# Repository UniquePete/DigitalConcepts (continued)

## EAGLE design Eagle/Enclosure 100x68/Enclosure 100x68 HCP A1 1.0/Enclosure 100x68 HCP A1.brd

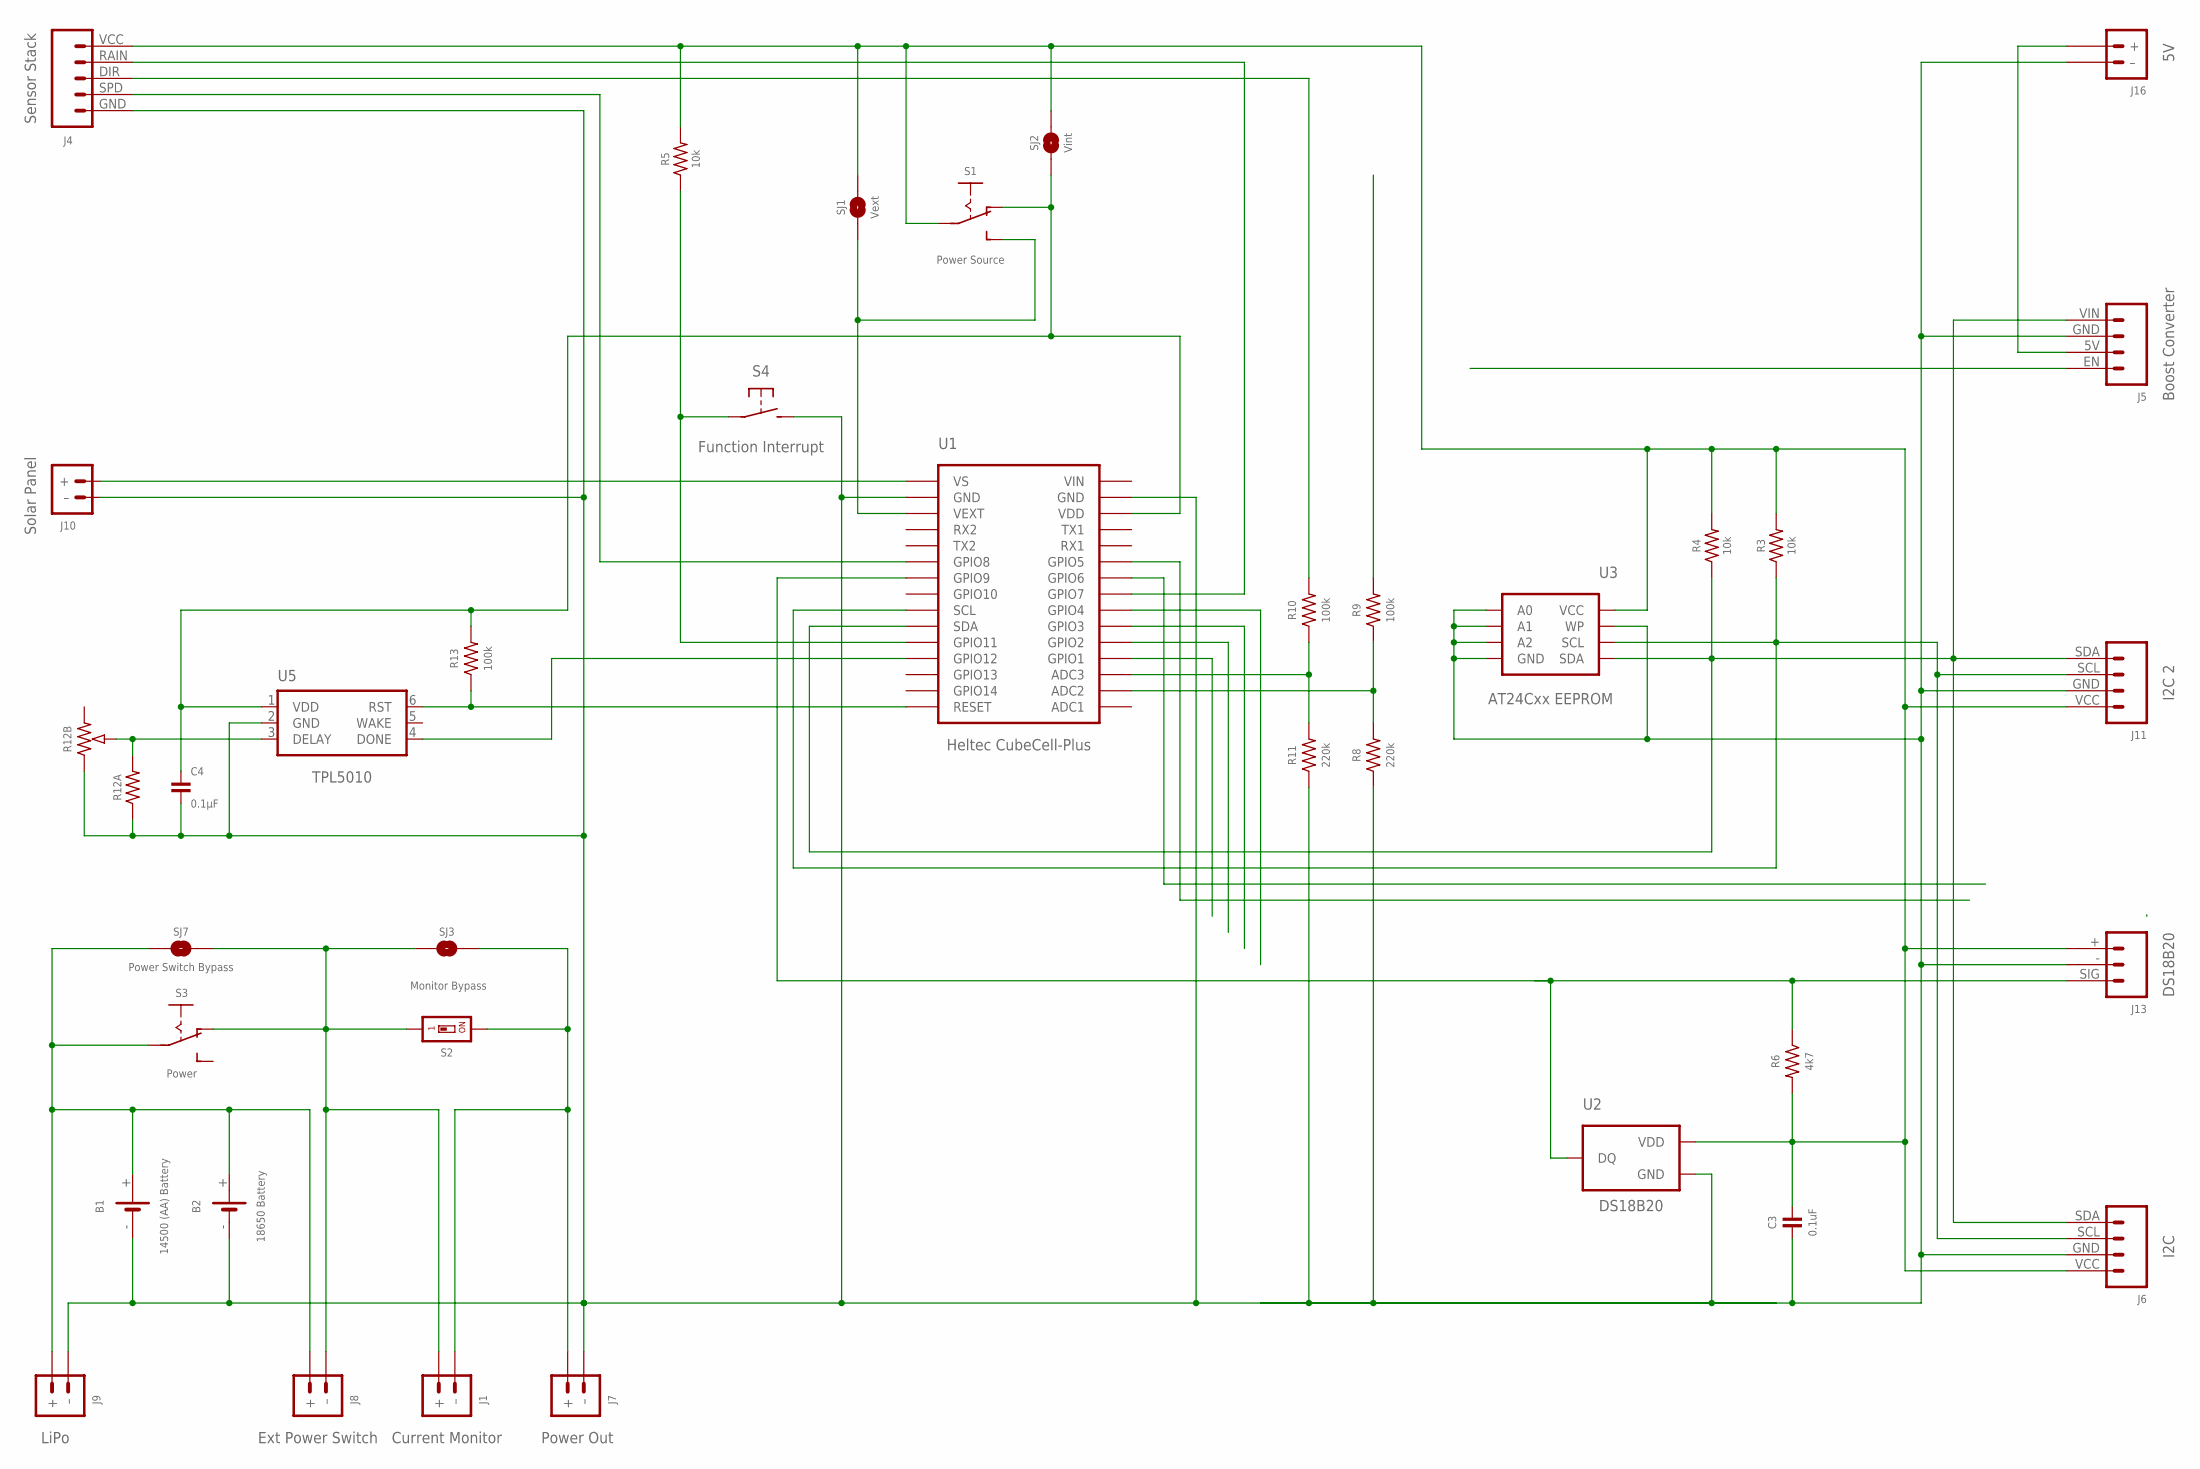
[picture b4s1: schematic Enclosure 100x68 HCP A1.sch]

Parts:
B1: 14500 (AA) Battery; BATTERY-14500
B2: 18650 Battery; BATTERY-18650
C3: 0.1uF; C0805
C4: 0.1µF; C0805
J1: Current Monitor; JST-PH2.0-2-HORIZONTAL
J4: Sensor Stack; JST-PH2.0-5-DUAL-WEATHER
J5: Boost Converter; CONN_04-FP6277
J6: I2C; CONN_04-I2C
J7: Power Out; JST-GH1.25-2-HORIZONTAL
J8: Ext Power Switch; JST-PH2.0-2-DUAL-POWER
J9: LiPo; JST-PH2.0-2-HORIZONTAL-POWER@1
J10: Solar Panel; JST-PH2.0-2-VERTICAL=POWER
J11: I2C 2; JST-PH2.0-4-HORIZONTAL
J13: DS18B20; JST-PH2.0-3-HORIZONTAL-DS18B20
J16: 5V; JST-PH2.0-2-HORIZONTAL-POWER
R3, R4, R5: 10k; R0805
R6: 4k7; R0805
R8, R11: 220k; R0805
R9, R10, R13: 100k; R0805
R12A: RESISTORR0805; R0805
R12B: RESISTOR-TRIMM-33-US; RTRIM3*3
S1: Power Source; SWITCH-SPDT-SMT
S2: Monitor Bypass; SMD-001
S3: Power; SWITCH-SPDT-PTH
S4: Function Interrupt; SWITCH-2-PAD
SJ1: Vext; SJ
SJ2: Vint; SJ-VIA-12
SJ3: Monitor; SJ
SJ7: Power Switch Bypass; SJ
U1: Heltec CubeCell-Plus; HELTEC-CUBECELL=PLUS-X
U2: DS18B20; TO-92
U3: AT24Cxx EEPROM; SOP-8
U5: TPL5010; SOT-23-6

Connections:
GND: B1.-, B2.-, C3.2, C4.2, J4.GND (5), J5.GND (3), J6.GND (2), J7.- (–), J9.- (–), J10.- (–), J11.GND (2), J13.- (2), J16.- (–), R8.1, R11.1, R12A.1, R12B.1 (A), S4.P$2 (S), U1.GND@14 (GND), U1.GND@17 (GND), U2.1 (GND), U3.P$1 (A0), U3.P$2 (A1), U3.P$3 (A2), U3.P$4 (GND), U3.P$7 (WP), U5.2 (GND)
unnamed: J10.+, U1.VS
unnamed: R10.1, R11.2, U1.ADC3
unnamed: J1.2 (–), J7.+, S2.2, SJ3.1
unnamed: B1.+, B2.+, J8.+, J9.+, S3.2, SJ7.2
unnamed: J4.DIR (3), R10.2
unnamed: J6.SCL (3), J11.SCL (3), R3.1, U1.SCL, U3.P$6 (SCL)
unnamed: J5.VIN (4), J6.SDA (4), J11.SDA (4), R4.1, U1.SDA, U3.P$5 (SDA)
unnamed: J4.SPD (4), U1.GPIO8
unnamed: S1.3 (S), SJ1.1, U1.VEXT
unnamed: R12A.2, R12B.2 (S), U5.3 (DELAY)
unnamed: J5.5V (2), J16.+
unnamed: J1.1 (+), J8.- (–), S2.1, S3.1 (O), SJ3.2, SJ7.1
unnamed: J13.SIG (1), R6.1, U1.GPIO9, U2.2 (DQ)
unnamed: R5.1, S4.P$1, U1.GPIO11
unnamed: J4.RAIN (2), U1.GPIO7
unnamed: R8.2, R9.1, U1.ADC2
unnamed: R13.1, U1.RST (RESET), U5.6 (RST)
unnamed: U1.GPIO12, U5.4 (DONE)
unnamed: C4.1, R13.2, S1.1 (O), SJ2.1, SJ2.1@V (1), U1.VDD, U5.1 (VDD)
VEXT: C3.1, J4.VCC (1), J6.VCC (1), J11.VCC (1), J13.+ (3), R3.2, R4.2, R5.2, R6.2, S1.2, SJ1.2, SJ2.2, SJ2.2@V (2), U2.3 (VDD), U3.P$8 (VCC)
VIN: U1.VIN

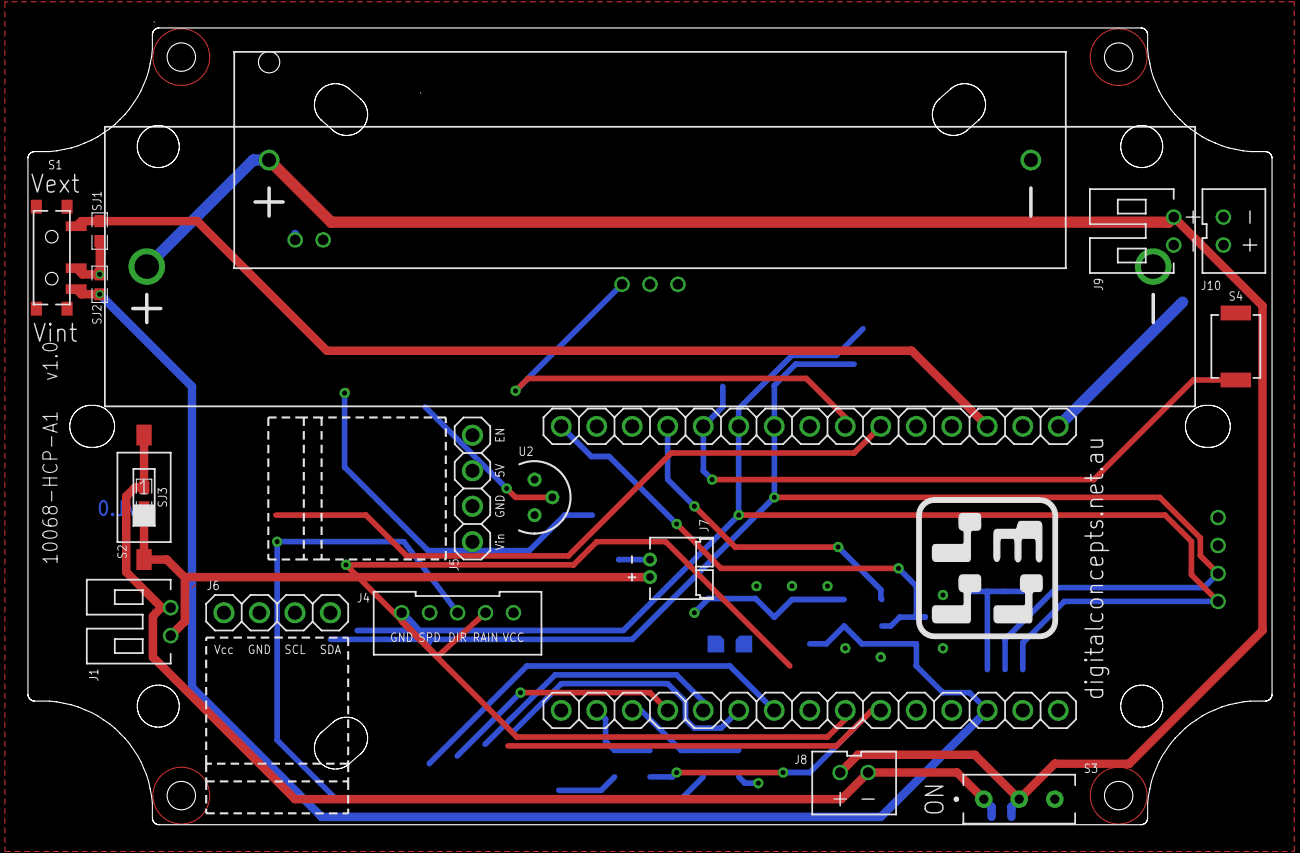
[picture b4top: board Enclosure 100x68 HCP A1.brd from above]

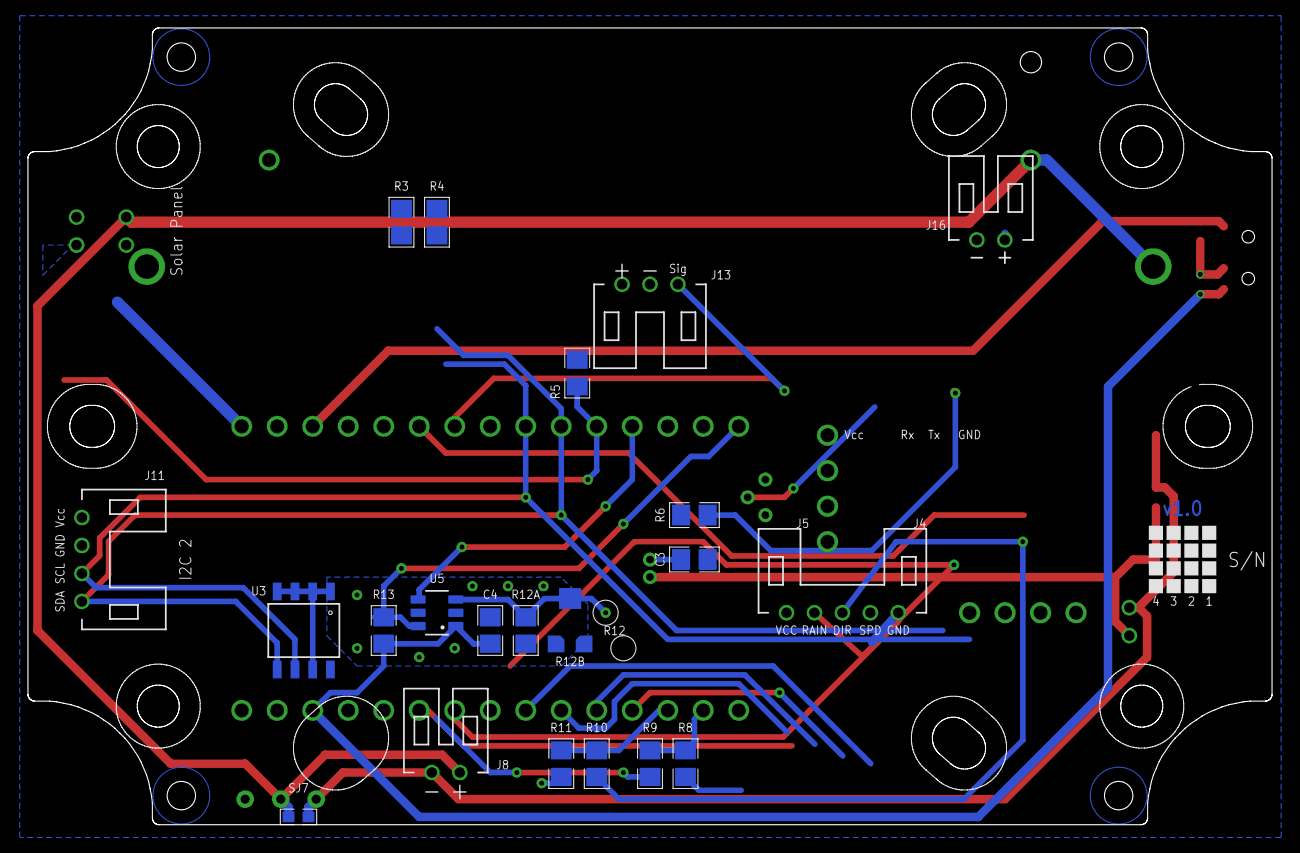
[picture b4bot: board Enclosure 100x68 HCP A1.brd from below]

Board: 2 copper layers, 89.0 x 57.0 mm, 38 parts (21 on the bottom side), 21 nets.
